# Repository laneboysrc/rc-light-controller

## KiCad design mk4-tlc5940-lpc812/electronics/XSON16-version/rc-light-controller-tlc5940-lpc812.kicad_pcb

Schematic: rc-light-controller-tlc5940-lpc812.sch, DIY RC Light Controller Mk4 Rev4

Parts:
C1: 1u/16V; C_0805_2012Metric
C2: 47u/6V3; C_0805_2012Metric
C3: 100n; C_0603_1608Metric
LED+1, LED+2: SMD50X100
OUT0, OUT1, OUT2, OUT3, OUT4, OUT5, OUT6, OUT7, OUT8, OUT9, OUT10, OUT11, OUT12, OUT13, OUT14, OUT15, OUT15S1: SMD50X100
PAD1: +; SMD80X120
PAD2: -; SMD80X120
PAD3: ST/Rx; SMD80X120
PAD4: TH/Tx; SMD80X120
PAD5: CH3; SMD80X120
PAD6: OUT/ISP; SMD80X120
R1: 2k0=20mA; R_0603_1608Metric
RN1: 1K; R_Array_Convex_4x0603
T1: NMOSSOT23; SOT-23
U1: 3V3; SOT-23W
U2: LPC812; NXP_XSON-16
U3: TLC5940PWP; SOP65P640X120-29N

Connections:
+3V3: C2.1, C3.2, U1.2, U2.12, U3.6, U3.26, U3.28
/AUX: RN1.7, U2.1
/AUX-IN: PAD5.1, RN1.2
/BLANK: U2.15, U3.2
/GSCLK: U2.9, U3.25
/IREF: R1.1, U3.27
/OUT0: OUT0.1, U3.7
/OUT1: OUT1.1, U3.8
/OUT2: OUT2.1, U3.9
/OUT3: OUT3.1, U3.10
/OUT4: OUT4.1, U3.11
/OUT5: OUT5.1, U3.12
/OUT6: OUT6.1, U3.13
/OUT7: OUT7.1, U3.14
/OUT8: OUT8.1, U3.15
/OUT9: OUT9.1, U3.16
/OUT10: OUT10.1, U3.17
/OUT11: OUT11.1, U3.18
/OUT12: OUT12.1, U3.19
/OUT13: OUT13.1, U3.20
/OUT14: OUT14.1, U3.21
/OUT15: OUT15.1, U3.22
/OUT15S: OUT15S1.1, T1.3
/OUT-ISP: RN1.6, U2.2
/OUT-ISP-OUT: PAD6.1, RN1.3
/OUT-SWITCHED: T1.1, U2.10
/SCLK: U2.6, U3.4
/SIN: U2.14, U3.5
/ST-IN: PAD3.1, RN1.1
/ST-RX: RN1.8, U2.16
/TH-IN: PAD4.1, RN1.4
/TH-TX: RN1.5, U2.4
/VIN: C1.1, LED+1.1, LED+2.1, PAD1.1, U1.3
/XLAT: U2.5, U3.3
GND: C1.2, C2.2, C3.1, PAD2.1, R1.2, T1.2, U1.1, U2.13, U3.1, U3.29

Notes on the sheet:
Special pins: PIO0_0 (16) ISP UART RX PIO0_4 ( 4) ISP UART TX PIO0_5 ( 3) RESET PIO0_10 ( 8) Open drain PIO0_11 ( 7) Open drain PIO0_2 ( 6) SWDIO PIO0_3 ( 5) SWCLK
Servo in/out
LED driver and outputs
Voltage regulator
Microcontroller
X7R
Input voltage range: 4 ... 10V
LDO: Microchip MCP1702 or MCP1703
X5R or X7R
NXP LPC812 ARM Cortex-M0 16K Flash, 4K RAM XSON-16
Switched output for light bar or similar
N-Channel MOSFET SOT23 package e.g. NXP PMV16UN
Polymer

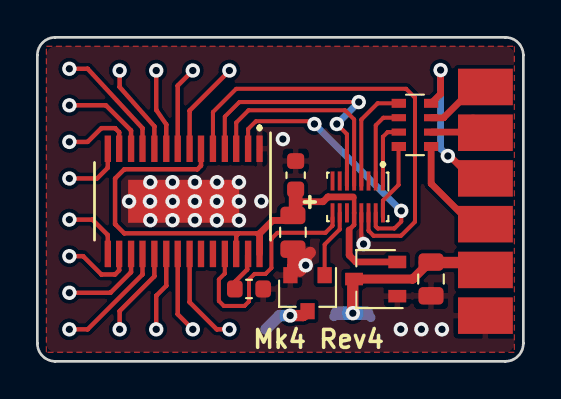
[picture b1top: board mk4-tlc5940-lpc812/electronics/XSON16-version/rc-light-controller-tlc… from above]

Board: 2 copper layers, 27.0 x 18.0 mm, 34 parts (0 on the bottom side), 35 nets.

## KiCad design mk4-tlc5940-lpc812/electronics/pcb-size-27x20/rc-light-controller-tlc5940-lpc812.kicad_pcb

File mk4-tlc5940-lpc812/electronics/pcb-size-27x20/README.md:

This folder contains the [KiCAD](http://kicad-pcb.org/) files for the MK4 TLC5940 LPC812 variant, revision 3, with a slightly larger board of 27 x 20 mm so that it can be assembled at JLCPCB.

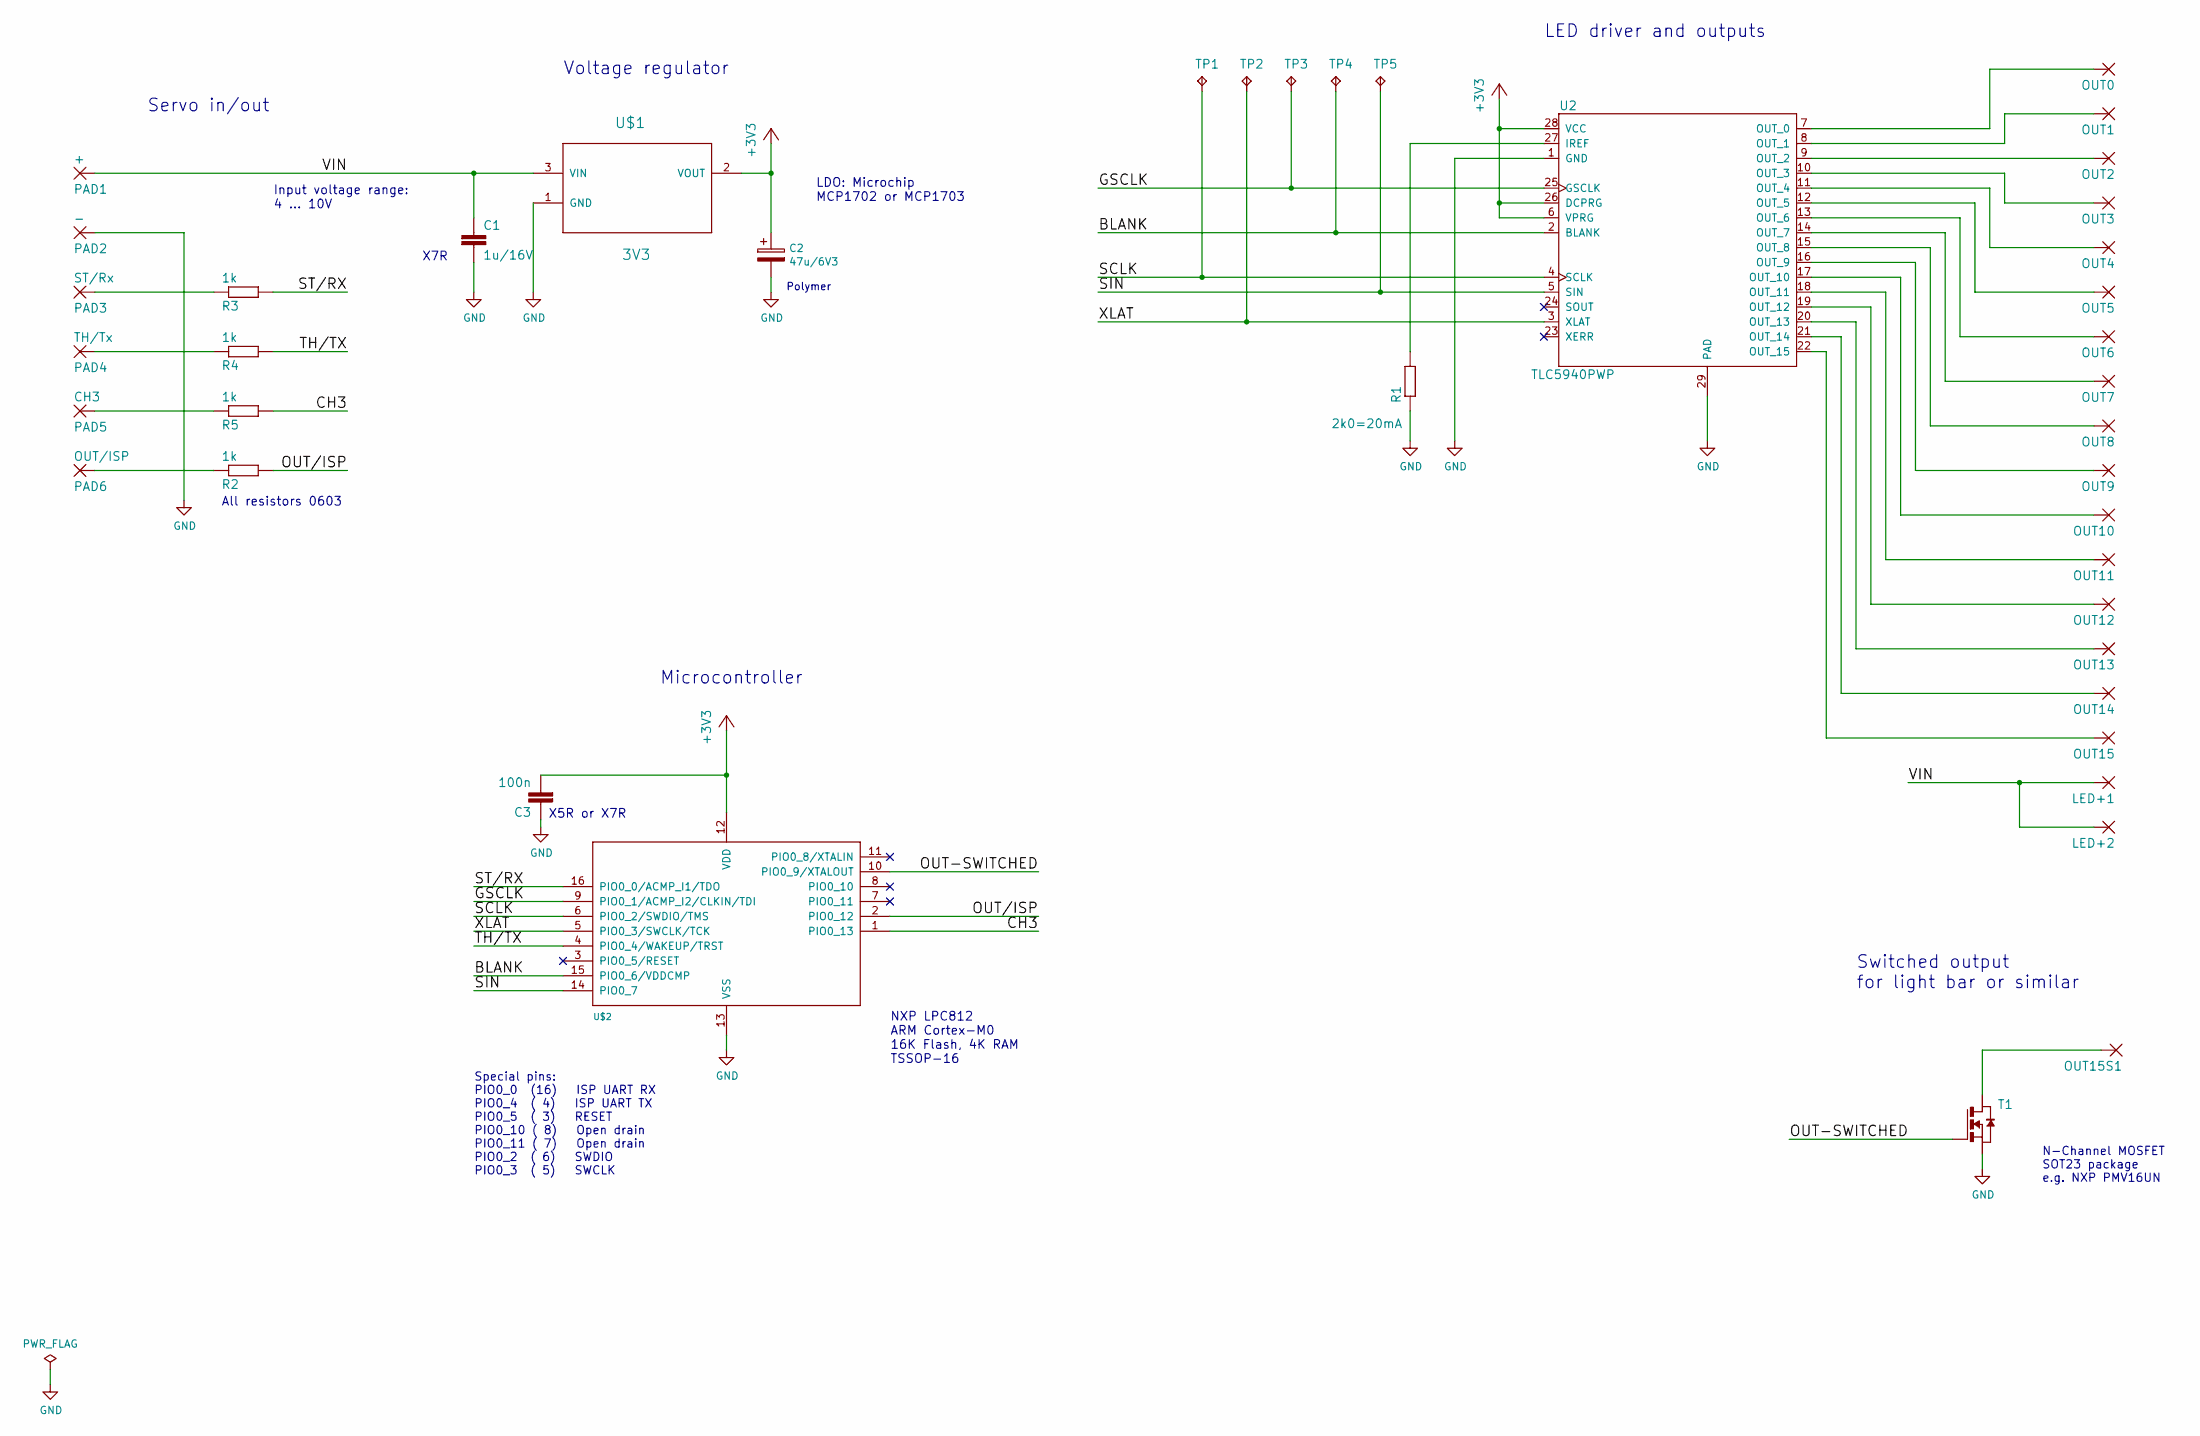
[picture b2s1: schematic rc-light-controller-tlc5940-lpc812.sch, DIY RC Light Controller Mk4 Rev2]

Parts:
C1: 1u/16V; C_0805_2012Metric
C2: 47u/6V3; C_0805_2012Metric
C3: 100n; C_0603_1608Metric
LED+1, LED+2: SMD50X100
OUT0, OUT1, OUT2, OUT3, OUT4, OUT5, OUT6, OUT7, OUT8, OUT9, OUT10, OUT11, OUT12, OUT13, OUT14, OUT15, OUT15S1: SMD50X100
PAD1: +; SMD80X120
PAD2: -; SMD80X120
PAD3: ST/Rx; SMD80X120
PAD4: TH/Tx; SMD80X120
PAD5: CH3; SMD80X120
PAD6: OUT/ISP; SMD80X120
R1: 2k0=20mA; R_0603_1608Metric
R2, R3, R4, R5: 1k; R_0603_1608Metric
T1: NMOSSOT23; SOT-23
TP1: SWDIO; TP10R
TP2, TP3, TP4, TP5: SWCLK; TP10R
U2: TLC5940PWP; SOP65P640X120-29N
U$1: 3V3; SOT95P300X145-3N
U$2: LPC812; TSSOP-16_4.4x5mm_P0.65mm

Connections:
+3V3: C2.1, C3.2, U2.6 (VPRG), U2.26 (DCPRG), U2.28 (VCC), U$1.2 (VOUT), U$2.12 (VDD)
/BLANK: TP4.TP, U2.2 (BLANK), U$2.15 (PIO0_6/VDDCMP)
/CH3: R5.2, U$2.1 (PIO0_13)
/GSCLK: TP3.TP, U2.25 (GSCLK), U$2.9 (PIO0_1/ACMP_I2/CLKIN/TDI)
/OUT-SWITCHED: T1.3 (G), U$2.10 (PIO0_9/XTALOUT)
/OUT/ISP: R2.2, U$2.2 (PIO0_12)
/SCLK: TP1.TP, U2.4 (SCLK), U$2.6 (PIO0_2/SWDIO/TMS)
/SIN: TP5.TP, U2.5 (SIN), U$2.14 (PIO0_7)
/ST/RX: R3.2, U$2.16 (PIO0_0/ACMP_I1/TDO)
/TH/TX: R4.2, U$2.4 (PIO0_4/WAKEUP/TRST)
/VIN: C1.1, LED+1.1, LED+2.1, PAD1.1, U$1.3 (VIN)
/XLAT: TP2.TP, U2.3 (XLAT), U$2.5 (PIO0_3/SWCLK/TCK)
GND: C1.2, C2.2, C3.1, PAD2.1, R1.1, T1.2 (S), U2.1 (GND), U2.29 (PAD), U$1.1 (GND), U$2.13 (VSS)
unnamed: OUT0.1, U2.7 (OUT_0)
unnamed: OUT1.1, U2.8 (OUT_1)
unnamed: OUT2.1, U2.9 (OUT_2)
unnamed: OUT3.1, U2.10 (OUT_3)
unnamed: OUT4.1, U2.11 (OUT_4)
unnamed: OUT5.1, U2.12 (OUT_5)
unnamed: OUT6.1, U2.13 (OUT_6)
unnamed: OUT7.1, U2.14 (OUT_7)
unnamed: OUT8.1, U2.15 (OUT_8)
unnamed: OUT9.1, U2.16 (OUT_9)
unnamed: OUT10.1, U2.17 (OUT_10)
unnamed: OUT11.1, U2.18 (OUT_11)
unnamed: OUT12.1, U2.19 (OUT_12)
unnamed: OUT13.1, U2.20 (OUT_13)
unnamed: OUT14.1, U2.21 (OUT_14)
unnamed: OUT15.1, U2.22 (OUT_15)
unnamed: OUT15S1.1, T1.1 (D)
unnamed: PAD3.1, R3.1
unnamed: PAD4.1, R4.1
unnamed: PAD5.1, R5.1
unnamed: PAD6.1, R2.1
unnamed: R1.2, U2.27 (IREF)

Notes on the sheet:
Special pins: PIO0_0 (16) ISP UART RX PIO0_4 ( 4) ISP UART TX PIO0_5 ( 3) RESET PIO0_10 ( 8) Open drain PIO0_11 ( 7) Open drain PIO0_2 ( 6) SWDIO PIO0_3 ( 5) SWCLK
Servo in/out
LED driver and outputs
Voltage regulator
Microcontroller
X7R
All resistors 0603
Input voltage range: 4 ... 10V
LDO: Microchip MCP1702 or MCP1703
X5R or X7R
NXP LPC812 ARM Cortex-M0 16K Flash, 4K RAM TSSOP-16
Switched output for light bar or similar
N-Channel MOSFET SOT23 package e.g. NXP PMV16UN
Polymer

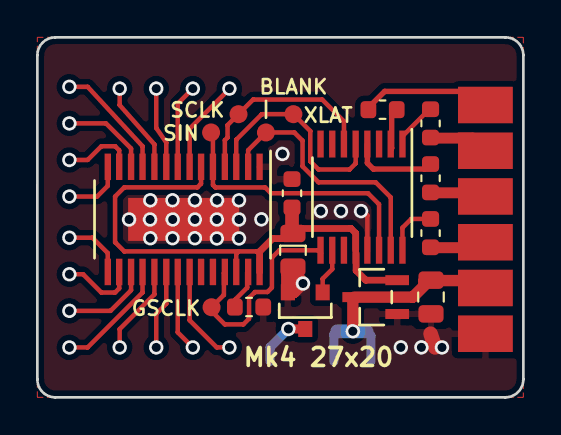
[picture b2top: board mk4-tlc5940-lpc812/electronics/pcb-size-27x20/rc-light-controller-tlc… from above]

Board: 2 copper layers, 27.0 x 20.0 mm, 42 parts (0 on the bottom side), 35 nets.

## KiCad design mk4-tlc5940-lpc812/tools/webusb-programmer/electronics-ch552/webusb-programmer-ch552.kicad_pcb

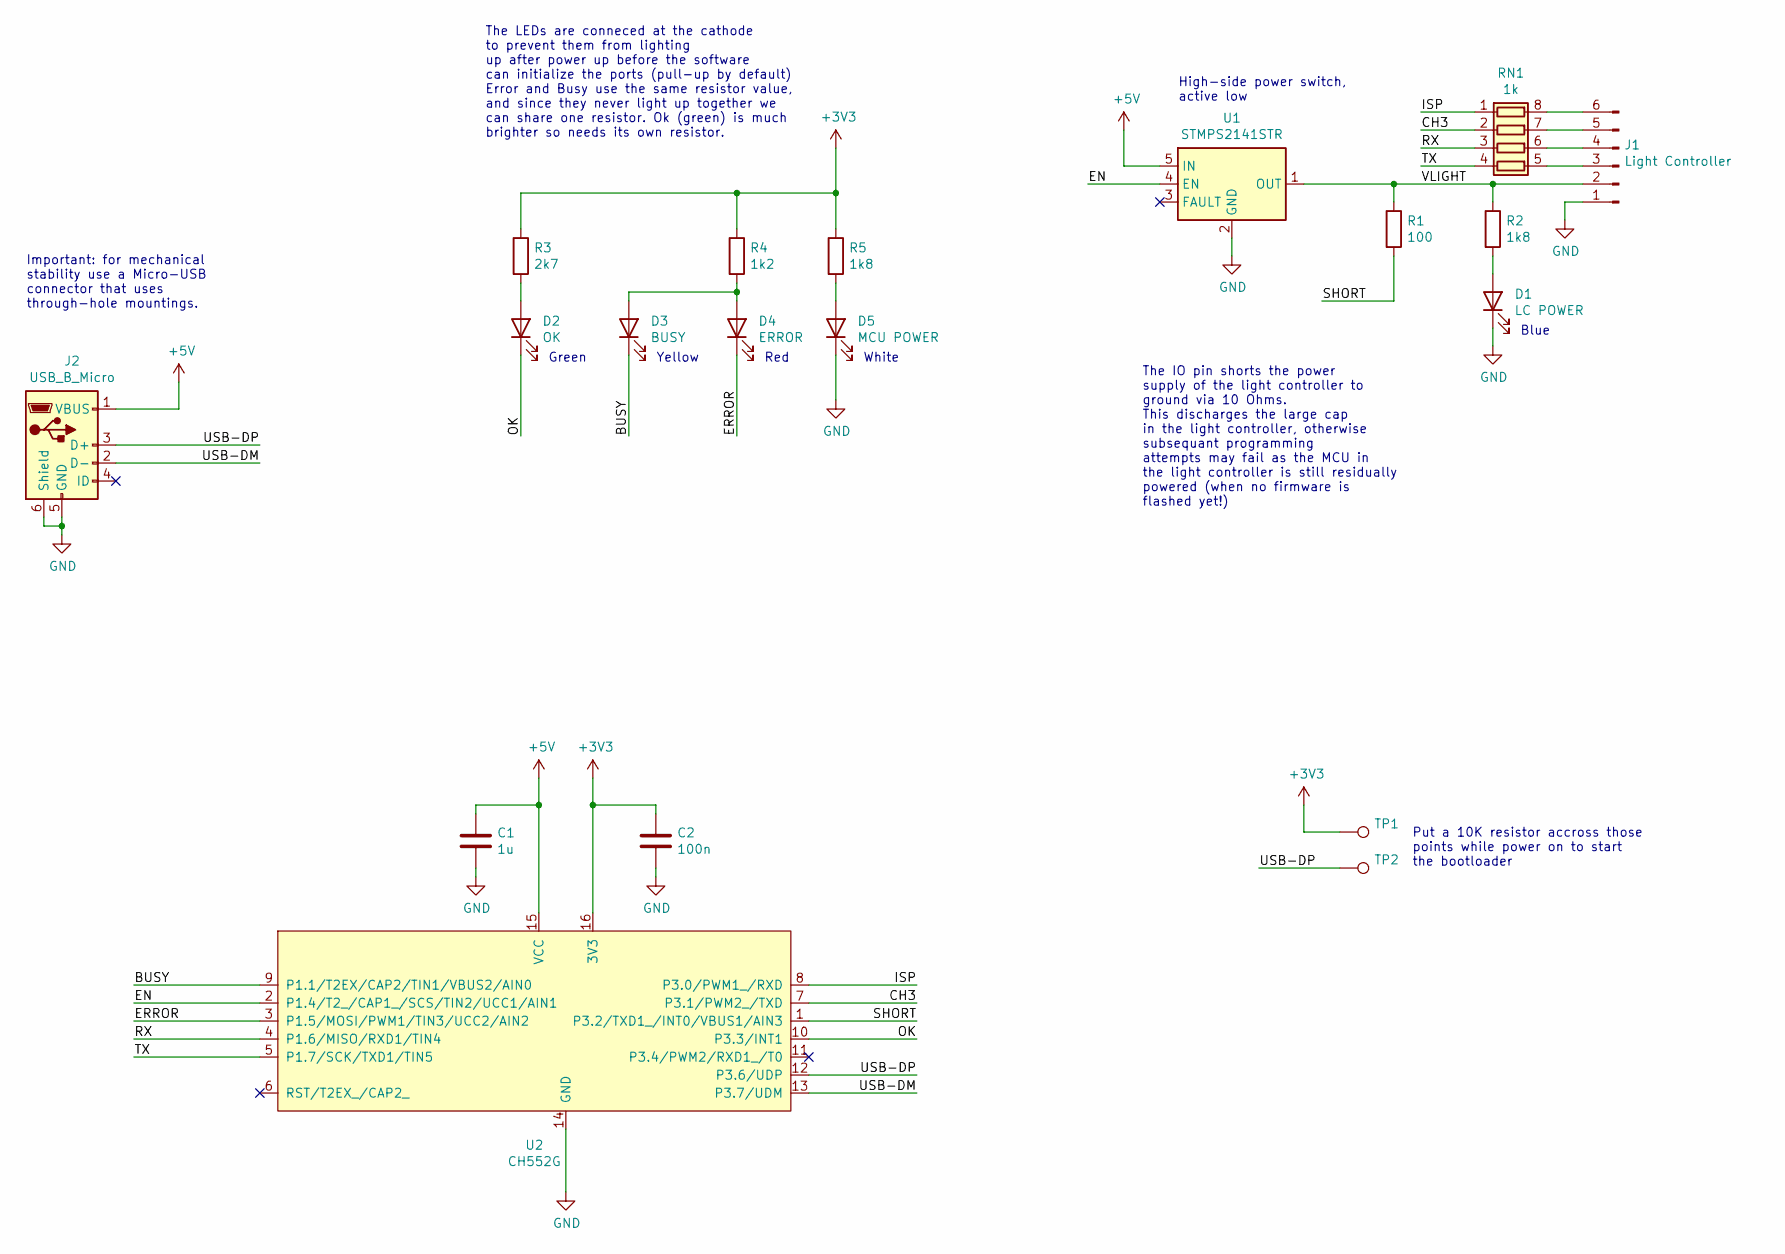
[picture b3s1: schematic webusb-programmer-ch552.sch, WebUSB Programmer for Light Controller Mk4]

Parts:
C1: 1u; C_0603_1608Metric
C2: 100n; C_0603_1608Metric
D1: LC POWER; LED_1204_side_mout; LCSC part number C779807
D2: OK; LED_1204_side_mout; LCSC part number C91608
D3: BUSY; LED_1204_side_mout; LCSC part number C779805
D4: ERROR; LED_1204_side_mout; LCSC part number C389527
D5: MCU POWER; LED_1204_side_mout; LCSC part number C779804
J1: Light Controller; PinHeader_1x06_P2.54mm_Flat
J2: USB_B_Micro; Mirco_USB_Type_B_LCSC_C40943; LCSC part number C40943
R1: 100; R_0603_1608Metric_Pad1.05x0.95mm_HandSolder
R2, R5: 1k8; R_0603_1608Metric_Pad1.05x0.95mm_HandSolder
R3: 2k7; R_0603_1608Metric_Pad1.05x0.95mm_HandSolder
R4: 1k2; R_0603_1608Metric_Pad1.05x0.95mm_HandSolder
RN1: 1k; R_Array_Convex_4x0603
TP1, TP2: TestPoint_THTPad_1.0x1.0mm_Drill0.5mm_nosilk
U1: STMPS2141STR; SOT-23-5
U2: CH552G; SO-16_3.9x9.9mm_P1.27mm

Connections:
+3V3: C2.1, R3.1, R4.1, R5.1, TP1.1, U2.16 (3V3)
+5V: C1.1, J2.1 (VBUS), U1.5 (IN), U2.15 (VCC)
/BUSY: D3.1 (K), U2.9 (P1.1/T2EX/CAP2/TIN1/VBUS2/AIN0)
/CH3: RN1.2 (R2.1), U2.7 (P3.1/PWM2_/TXD)
/EN: U1.4 (EN), U2.2 (P1.4/T2_/CAP1_/SCS/TIN2/UCC1/AIN1)
/ERROR: D4.1 (K), U2.3 (P1.5/MOSI/PWM1/TIN3/UCC2/AIN2)
/ISP: RN1.1 (R1.1), U2.8 (P3.0/PWM1_/RXD)
/OK: D2.1 (K), U2.10 (P3.3/INT1)
/RX: RN1.3 (R3.1), U2.4 (P1.6/MISO/RXD1/TIN4)
/SHORT: R1.2, U2.1 (P3.2/TXD1_/INT0/VBUS1/AIN3)
/TX: RN1.4 (R4.1), U2.5 (P1.7/SCK/TXD1/TIN5)
/USB-DM: J2.2 (D-), U2.13 (P3.7/UDM)
/USB-DP: J2.3 (D+), TP2.1, U2.12 (P3.6/UDP)
/VLIGHT: J1.2, R1.1, R2.1, U1.1 (OUT)
GND: C1.2, C2.2, D1.1 (K), D5.1 (K), J1.1, J2.5 (GND), J2.6 (Shield), U1.2 (GND), U2.14 (GND)
unnamed: D1.2 (A), R2.2
unnamed: D2.2 (A), R3.2
unnamed: D3.2 (A), D4.2 (A), R4.2
unnamed: D5.2 (A), R5.2
unnamed: J1.3, RN1.5 (R4.2)
unnamed: J1.4, RN1.6 (R3.2)
unnamed: J1.5, RN1.7 (R2.2)
unnamed: J1.6, RN1.8 (R1.2)

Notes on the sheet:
Important: for mechanical stability use a Micro-USB connector that uses through-hole mountings.
The IO pin shorts the power supply of the light controller to ground via 10 Ohms. This discharges the large cap in the light controller, otherwise subsequant programming attempts may fail as the MCU in the light controller is still residually powered (when no firmware is flashed yet!)
High-side power switch, active low
White
Green
Yellow
Red
Blue
The LEDs are conneced at the cathode to prevent them from lighting up after power up before the software can initialize the ports (pull-up by default) Error and Busy use the same resistor value, and since they never light up together we can share one resistor. Ok (green) is much brighter so needs i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
Put a 10K resistor accross those points while power on to start the bootloader

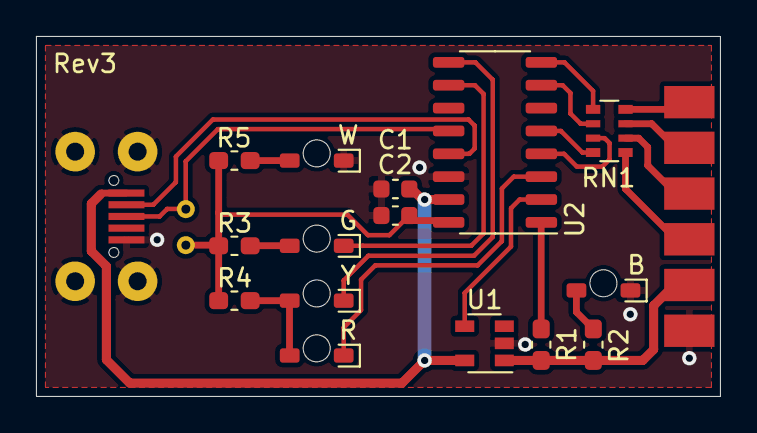
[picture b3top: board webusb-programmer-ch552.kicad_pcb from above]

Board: 2 copper layers, 38.0 x 20.0 mm, 19 parts (0 on the bottom side), 23 nets.

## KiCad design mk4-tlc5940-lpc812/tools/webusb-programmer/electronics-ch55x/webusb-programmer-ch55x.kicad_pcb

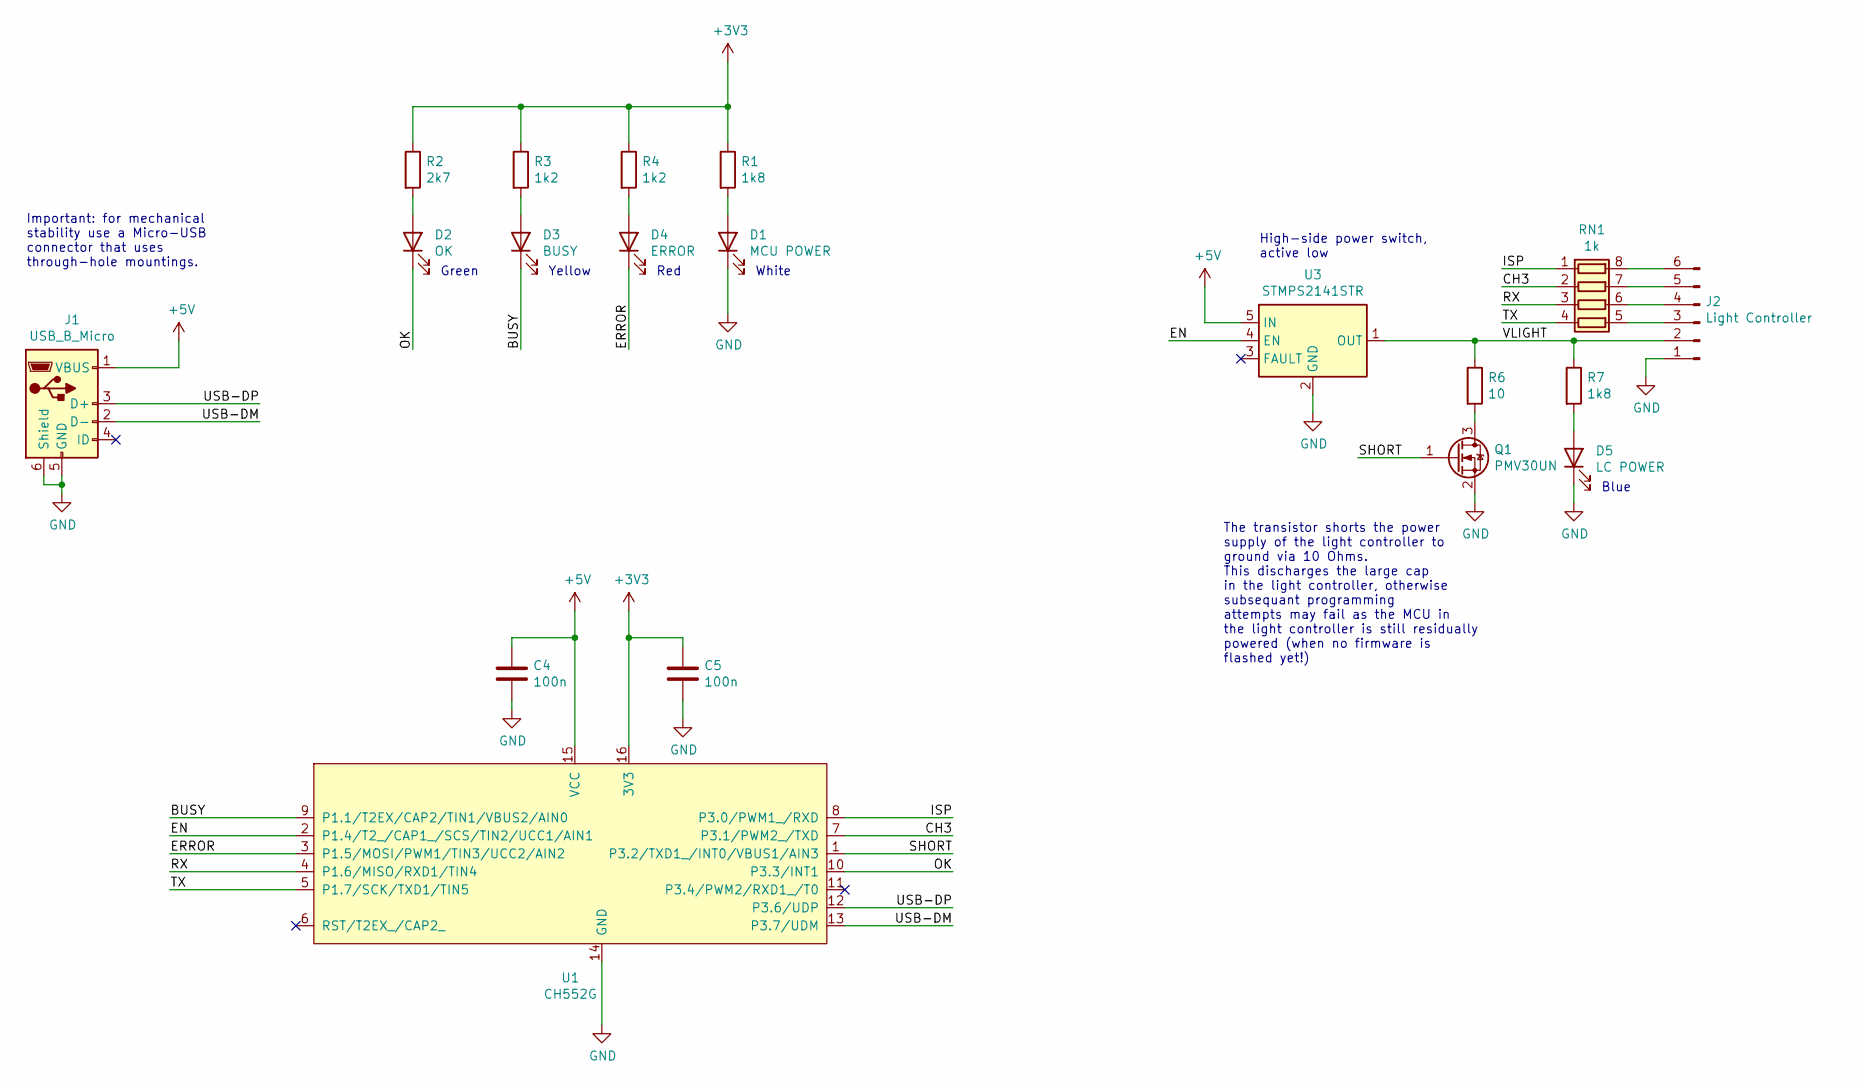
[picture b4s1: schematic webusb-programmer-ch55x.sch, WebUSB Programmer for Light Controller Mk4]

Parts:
C4, C5: 100n; C_0603_1608Metric
D1: MCU POWER; LED_1204_reverse_mout; LCSC part number C779804
D2: OK; LED_1204_reverse_mout; LCSC part number C91608
D3: BUSY; LED_1204_reverse_mout; LCSC part number C779805
D4: ERROR; LED_1204_reverse_mout; LCSC part number C389527
D5: LC POWER; LED_1204_reverse_mout; LCSC part number C779807
J1: USB_B_Micro; Mirco_USB_Type_B_LCSC_C40943; LCSC part number C40943
J2: Light Controller; PinHeader_1x06_P2.54mm_Flat
Q1: PMV30UN; SOT-23
R1, R7: 1k8; R_0603_1608Metric_Pad1.05x0.95mm_HandSolder
R2: 2k7; R_0603_1608Metric_Pad1.05x0.95mm_HandSolder
R3, R4: 1k2; R_0603_1608Metric_Pad1.05x0.95mm_HandSolder
R6: 10; R_0603_1608Metric_Pad1.05x0.95mm_HandSolder
RN1: 1k; R_Array_Convex_4x0603
U1: CH552G; SO-16_3.9x9.9mm_P1.27mm
U3: STMPS2141STR; SOT-23-5

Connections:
+3V3: C5.1, R1.1, R2.1, R3.1, R4.1, U1.16 (3V3)
+5V: C4.1, J1.1 (VBUS), U1.15 (VCC), U3.5 (IN)
/BUSY: D3.1 (K), U1.9 (P1.1/T2EX/CAP2/TIN1/VBUS2/AIN0)
/CH3: RN1.2 (R2.1), U1.7 (P3.1/PWM2_/TXD)
/EN: U1.2 (P1.4/T2_/CAP1_/SCS/TIN2/UCC1/AIN1), U3.4 (EN)
/ERROR: D4.1 (K), U1.3 (P1.5/MOSI/PWM1/TIN3/UCC2/AIN2)
/ISP: RN1.1 (R1.1), U1.8 (P3.0/PWM1_/RXD)
/OK: D2.1 (K), U1.10 (P3.3/INT1)
/RX: RN1.3 (R3.1), U1.4 (P1.6/MISO/RXD1/TIN4)
/SHORT: Q1.1 (G), U1.1 (P3.2/TXD1_/INT0/VBUS1/AIN3)
/TX: RN1.4 (R4.1), U1.5 (P1.7/SCK/TXD1/TIN5)
/USB-DM: J1.2 (D-), U1.13 (P3.7/UDM)
/USB-DP: J1.3 (D+), U1.12 (P3.6/UDP)
/VLIGHT: J2.2, R6.1, R7.1, U3.1 (OUT)
GND: C4.2, C5.2, D1.1 (K), D5.1 (K), J1.5 (GND), J1.6 (Shield), J2.1, Q1.2 (S), U1.14 (GND), U3.2 (GND)
unnamed: D1.2 (A), R1.2
unnamed: D2.2 (A), R2.2
unnamed: D3.2 (A), R3.2
unnamed: D4.2 (A), R4.2
unnamed: D5.2 (A), R7.2
unnamed: J2.3, RN1.5 (R4.2)
unnamed: J2.4, RN1.6 (R3.2)
unnamed: J2.5, RN1.7 (R2.2)
unnamed: J2.6, RN1.8 (R1.2)
unnamed: Q1.3 (D), R6.2

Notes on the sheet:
Important: for mechanical stability use a Micro-USB connector that uses through-hole mountings.
The transistor shorts the power supply of the light controller to ground via 10 Ohms. This discharges the large cap in the light controller, otherwise subsequant programming attempts may fail as the MCU in the light controller is still residually powered (when no firmware is flashed yet!)
High-side power switch, active low
White
Green
Yellow
Red
Blue

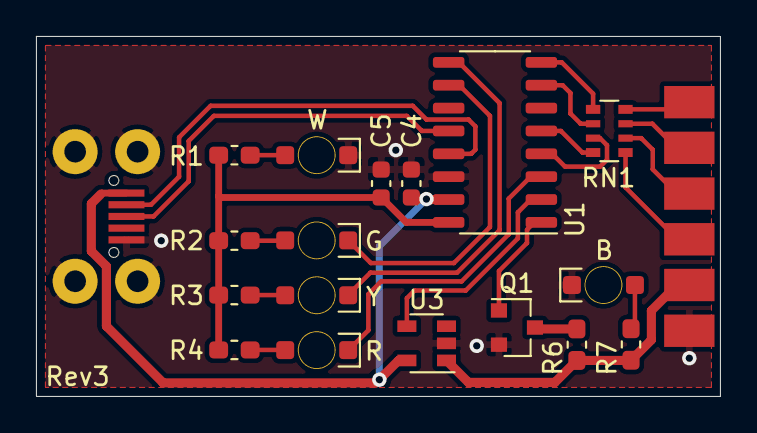
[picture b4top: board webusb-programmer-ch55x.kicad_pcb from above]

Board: 2 copper layers, 38.0 x 20.0 mm, 19 parts (0 on the bottom side), 25 nets.
